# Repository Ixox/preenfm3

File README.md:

# preenFM3

preenFM3 is an open-source FM synthesizer built around an STM32H7 microcontroller.

This repository contains the firmware, the shared hardware library, the bootloader and the hardware design files.

Binaries are available in the [Releases](https://github.com/Ixox/preenfm3/releases) section.  
More user documentation is available in the [Wiki](https://github.com/Ixox/preenfm3/wiki).

## Overview

The firmware runs the FM synth engine, the display UI, MIDI input/output, SD card storage and the bootloader.

The project is split into:

| Folder | Contents |
|--------|----------|
| `firmware/` | Main synth firmware |
| `preen_lib/` | Shared display, input, board and storage library |
| `third_party/` | Vendored HAL, CMSIS, USB, FatFs, SD, display and helper libraries |
| `bootloader/` | Standalone bootloader |
| `hardware/` | PCB and mechanical files |
| `doc/` | Hardware, compilation and improvement notes |

## Hardware at a glance

| Subsystem | Details |
|-----------|---------|
| MCU | STM32H753VITx, Cortex-M7, 480 MHz |
| Audio output | 3 × CS4344 stereo DACs, 6 analog outputs |
| Audio transport | SAI1/SAI2 in I2S mode, DMA, 48 kHz |
| Display | ILI9341, 240 × 320 RGB565, SPI1 + DMA2D |
| Storage | microSD card in SPI mode, SPI2 + FatFs |
| Controls | 6 encoders and 12/18 buttons through a 74HC165 chain |
| MIDI | DIN MIDI on USART1 and USB MIDI over OTG FS |
| Memory | RAM_D1 for display, RAM_D2 for DAC/FX, RAM_D2B for FatFs, RAM_D3 for sequencer |

The CPU runs at its rated 480 MHz; it is not overclocked. The ILI9341 SPI bus runs at approximately 32 MHz, above the panel's nominal rating.

See [doc/hardware.md](doc/hardware.md) for the full hardware documentation.

## Building

The project builds with **CMake** at the repository root. The legacy STM32CubeIDE project files remain in the tree as reference.

The main firmware build configurations are:

| Configuration | Optimization | Debug |
|---------------|--------------|-------|
| `Debug` | `-Og` | `-g3` |
| `Release` (default) | `-Ofast -fno-strict-aliasing -fno-tree-vectorize -funroll-loops` | `-g0` |

Common build settings:

- Toolchain: GNU Arm Embedded (`arm-none-eabi-`), validated with `arm-none-eabi-gcc` 16.2.0
- MCU: `STM32H753VITx`
- Defines: `USE_HAL_DRIVER`, `STM32H753xx`
- Firmware linker script: `firmware/preenfm3_2MB.ld`
- Bootloader linker script: `bootloader/STM32H753VITX_FLASH.ld`

### CMake

Requirements:

- CMake 3.20 or newer
- `arm-none-eabi-gcc` — validated with version 16.2.0
- `arm-none-eabi-newlib` — validated with version 4.6.0.20260123

Configure and build:

```bash
cmake -S . -B build -DCMAKE_TOOLCHAIN_FILE=cmake/arm-none-eabi.cmake
cmake --build build
```

This builds both `preenfm3_firmware` and `preenfm3_bootloader`. The default `Release` build produces `build/firmware/p3_<version>.bin` and `build/bootloader/p3_boot_<version>.bin`, along with the `.elf`, `.bin` and `.hex` artifacts. The firmware version comes from `firmware/include/version.h` (currently `v1.04`, so `p3_1_04.bin`); the bootloader version comes from `bootloader/include/version.h`.

### Flashing

There are two separate operations: flashing the **bootloader** (only needed once, or to upgrade it) and flashing the **firmware**.

To boot into the bootloader, hold down the **MENU** button while turning the preenFM3 on.

#### Bootloader (first-time / never-flashed board)

The bootloader lives at `0x08000000` and must be installed before the firmware can be updated normally. On a board that has never been flashed, put the MCU in DFU mode with the switch on the back of the PCB, then flash the bootloader:

```bash
dfu-util -a 0 -d 0x0483:0xdf11 \
  -D build/bootloader/p3_boot_1_10.bin -s 0x08000000
```

Alternatively, use ST-LINK through the 4-pin header on the back of the PCB; see [doc/stlink.md](doc/stlink.md).

Once the bootloader has been flashed, you can enter DFU mode from the bootloader itself, or keep using the ST-LINK 4-pin header.

#### Firmware (normal update)

The preferred method is the SD card:

1. Put `build/firmware/p3_<version>.bin` (for example `p3_1_04.bin`) on the SD card.
2. Boot the bootloader and flash the file from the SD card.

If the SD card is not accessible, the bootloader can expose it to a computer as a USB mass-storage device, so the firmware `.bin` can be copied without removing the card.

Firmware updates can also be done over DFU from the bootloader:

```bash
dfu-util -a 0 -d 0x0483:0xdf11 \
  -D build/firmware/p3_1_04.bin -s 0x08020000
```

Finally, the firmware can be written directly with ST-LINK through the 4-pin header on the back of the PCB:

```bash
st-flash --reset write build/firmware/p3_1_04.bin 0x08020000
```

See [doc/stlink.md](doc/stlink.md) for ST-LINK setup and troubleshooting.

### Project status

The source tree has been reorganized into `firmware/`, `preen_lib/`, `third_party/` and `bootloader/`. The CMake build now produces the full firmware and bootloader; the CubeIDE `.cproject` files are no longer the primary build.

See [doc/compilation.md](doc/compilation.md) for detailed build information and the CMake migration plan.

## Documentation

- [Hardware documentation](doc/hardware.md)
- [Compilation and CMake migration](doc/compilation.md)
- [Known improvements](doc/improvements.md)
- [Project Wiki](https://github.com/Ixox/preenfm3/wiki)

## License

The firmware is distributed under the GNU General Public License v3. See [LICENSE](LICENSE) for the full text and [third_party/NOTICE](third_party/NOTICE) for third-party licensing. See the source file headers for details.

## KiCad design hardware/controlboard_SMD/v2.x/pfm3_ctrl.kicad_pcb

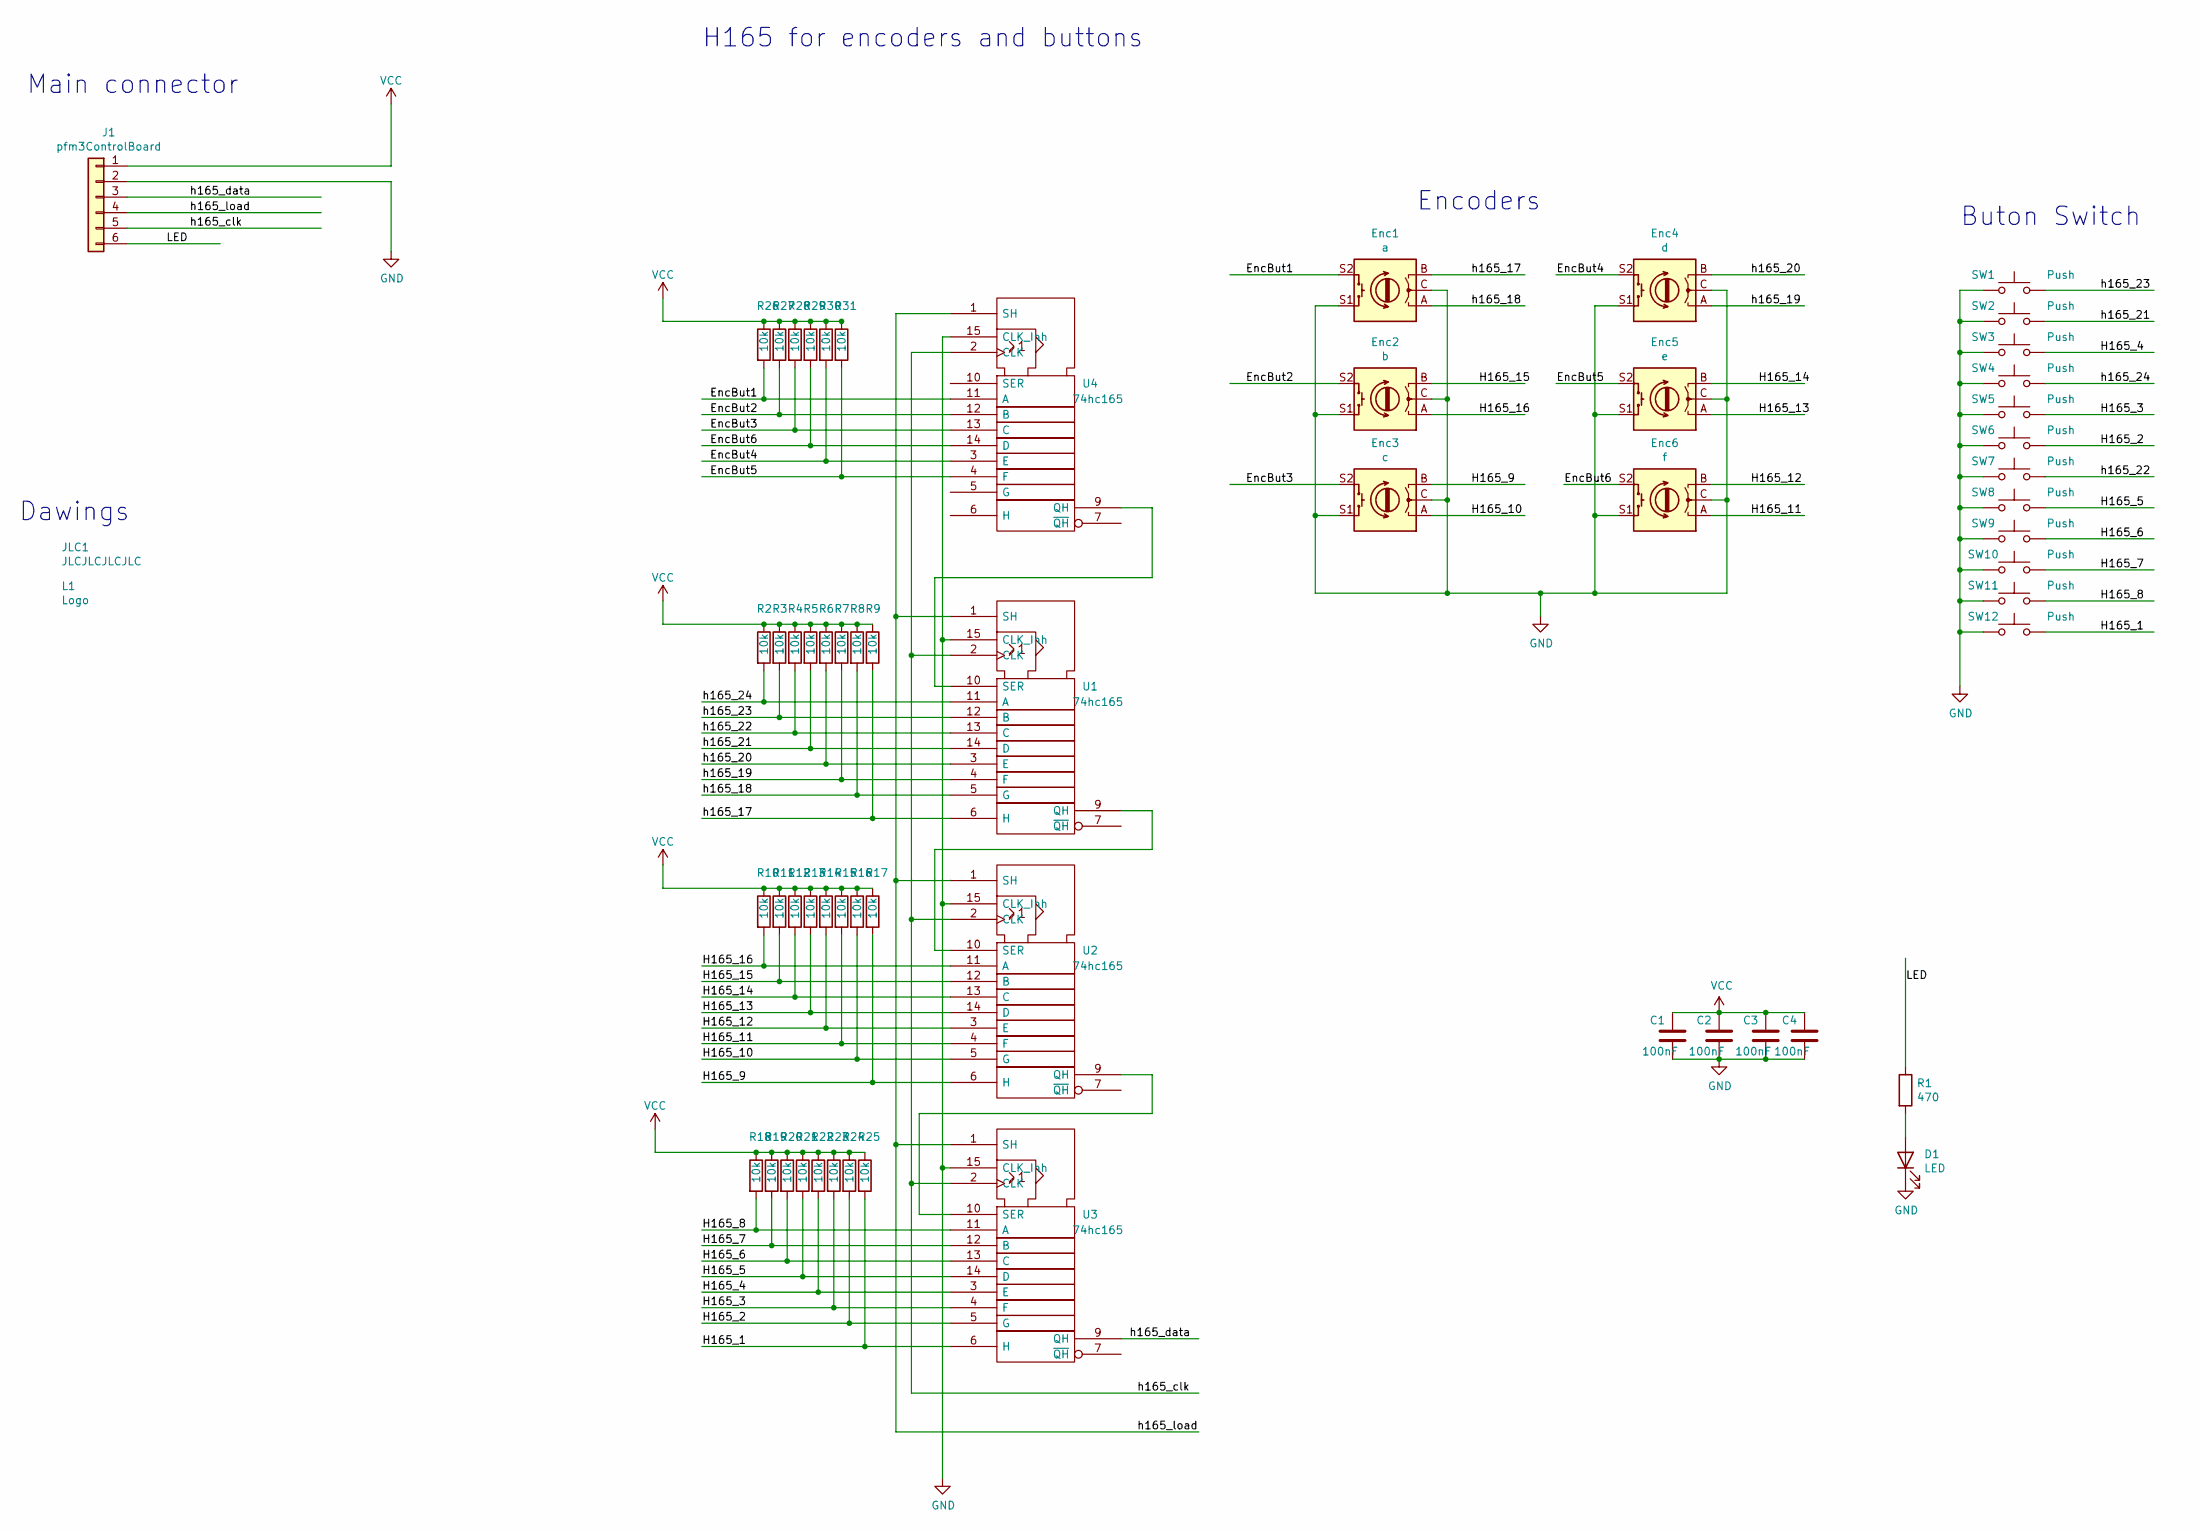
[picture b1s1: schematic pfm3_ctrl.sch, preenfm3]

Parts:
C1, C2, C3, C4: 100nF; C_0402_1005Metric
D1: LED; LED_0603_1608Metric
Enc1: a; FMEncoder2_pfm3
Enc2: b; FMEncoder2_pfm3
Enc3: c; FMEncoder2_pfm3
Enc4: d; FMEncoder2_pfm3
Enc5: e; FMEncoder2_pfm3
Enc6: f; FMEncoder2_pfm3
J1: pfm3ControlBoard; ControlBoard_2
JLC1: JLCJLCJLCJLC; JLCJLC
L1: Logo; pfm2_logo
R1: 470; R_0603_1608Metric
R2, R3, R4, R5, R6, R7, R8, R9, R10, R11, R12, R13, R14, R15, R16, R17, R18, R19, R20, R21, R22, R23, R24, R25, R26, R27, R28, R29, R30, R31: 10k; R_0402_1005Metric
SW1, SW2, SW3, SW4, SW5, SW6, SW7, SW8, SW9, SW10, SW11, SW12: Push; FMButton2
U1, U2, U3, U4: 74hc165; SOIC-16_3.9x9.9mm_P1.27mm

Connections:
/EncBut1: Enc1.S2, R26.2, U4.11 (A)
/EncBut2: Enc2.S2, R27.2, U4.12 (B)
/EncBut3: Enc3.S2, R28.2, U4.13 (C)
/EncBut4: Enc4.S2, R30.2, U4.3 (E)
/EncBut5: Enc5.S2, R31.2, U4.4 (F)
/EncBut6: Enc6.S2, R29.2, U4.14 (D)
/H165_1: R25.2, SW12.2, U3.6 (H)
/H165_2: R24.2, SW6.2, U3.5 (G)
/H165_3: R23.2, SW5.2, U3.4 (F)
/H165_4: R22.2, SW3.2, U3.3 (E)
/H165_5: R21.2, SW8.2, U3.14 (D)
/H165_6: R20.2, SW9.2, U3.13 (C)
/H165_7: R19.2, SW10.2, U3.12 (B)
/H165_8: R18.2, SW11.2, U3.11 (A)
/H165_9: Enc3.B, R17.2, U2.6 (H)
/H165_10: Enc3.A, R16.2, U2.5 (G)
/H165_11: Enc6.A, R15.2, U2.4 (F)
/H165_12: Enc6.B, R14.2, U2.3 (E)
/H165_13: Enc5.A, R13.2, U2.14 (D)
/H165_14: Enc5.B, R12.2, U2.13 (C)
/H165_15: Enc2.B, R11.2, U2.12 (B)
/H165_16: Enc2.A, R10.2, U2.11 (A)
/LED: J1.6, R1.1
/h165_17: Enc1.B, R9.2, U1.6 (H)
/h165_18: Enc1.A, R8.2, U1.5 (G)
/h165_19: Enc4.A, R7.2, U1.4 (F)
/h165_20: Enc4.B, R6.2, U1.3 (E)
/h165_21: R5.2, SW2.2, U1.14 (D)
/h165_22: R4.2, SW7.2, U1.13 (C)
/h165_23: R3.2, SW1.2, U1.12 (B)
/h165_24: R2.2, SW4.2, U1.11 (A)
/h165_clk: J1.5, U1.2 (CLK), U2.2 (CLK), U3.2 (CLK), U4.2 (CLK)
/h165_data: J1.3, U3.9 (QH)
/h165_load: J1.4, U1.1 (SH), U2.1 (SH), U3.1 (SH), U4.1 (SH)
GND: C1.2, C2.2, C3.2, C4.2, D1.1 (K), Enc1.C, Enc1.S1, Enc2.C, Enc2.S1, Enc3.C, Enc3.S1, Enc4.C, Enc4.S1, Enc5.C, Enc5.S1, Enc6.C, Enc6.S1, J1.2, SW1.1, SW2.1, SW3.1, SW4.1, SW5.1, SW6.1, SW7.1, SW8.1, SW9.1, SW10.1, SW11.1, SW12.1, U1.8 (GND), U1.15 (CLK_Inh), U2.8 (GND), U2.15 (CLK_Inh), U3.8 (GND), U3.15 (CLK_Inh), U4.8 (GND), U4.15 (CLK_Inh)
unnamed: D1.2 (A), R1.2
unnamed: U1.9 (QH), U2.10 (SER)
unnamed: U1.10 (SER), U4.9 (QH)
unnamed: U2.9 (QH), U3.10 (SER)
VCC: C1.1, C2.1, C3.1, C4.1, J1.1, R2.1, R3.1, R4.1, R5.1, R6.1, R7.1, R8.1, R9.1, R10.1, R11.1, R12.1, R13.1, R14.1, R15.1, R16.1, R17.1, R18.1, R19.1, R20.1, R21.1, R22.1, R23.1, R24.1, R25.1, R26.1, R27.1, R28.1, R29.1, R30.1, R31.1, U1.16 (VCC), U2.16 (VCC), U3.16 (VCC), U4.16 (VCC)

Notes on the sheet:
Buton Switch
Encoders
H165 for encoders and buttons
Main connector
Dawings

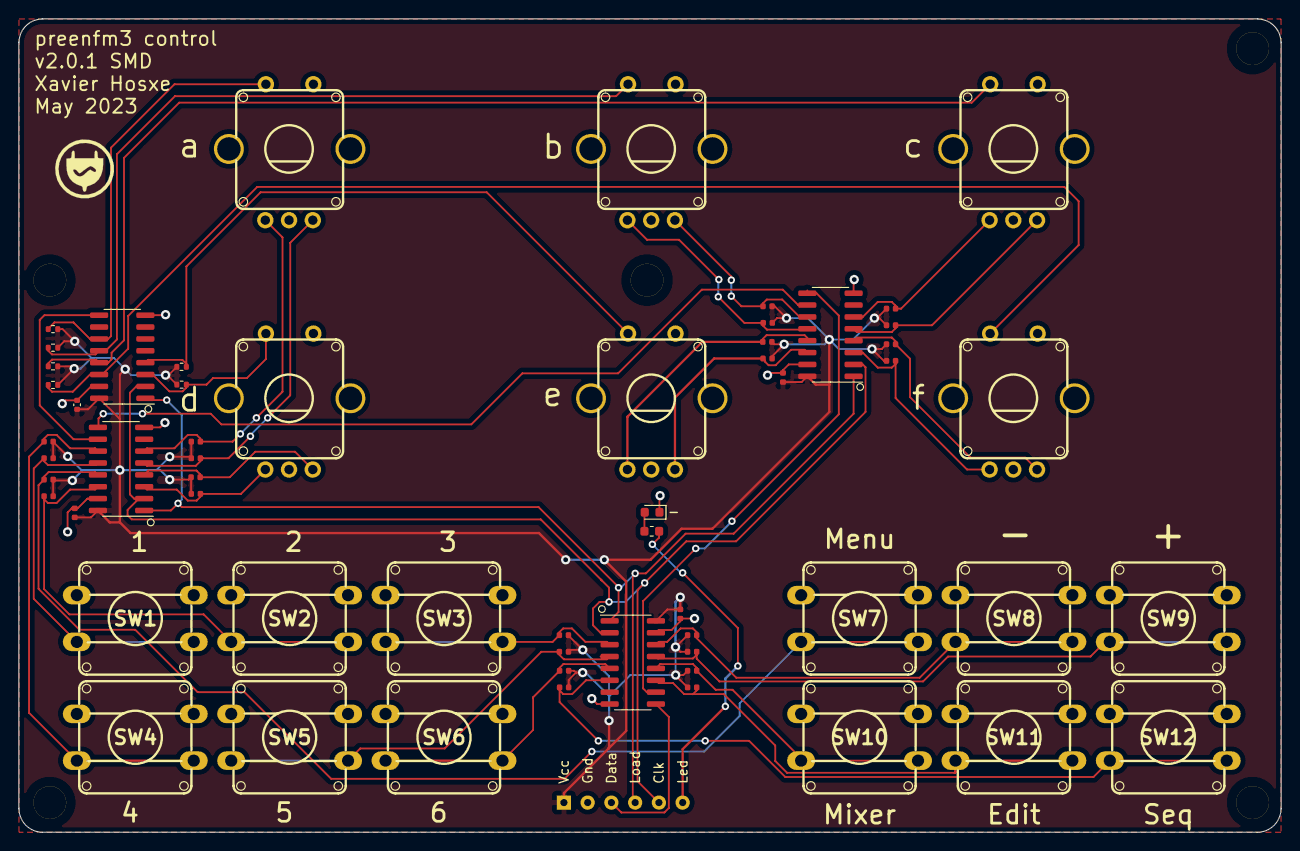
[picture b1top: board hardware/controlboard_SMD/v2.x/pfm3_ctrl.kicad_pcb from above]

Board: 2 copper layers, 135.0 x 87.0 mm, 61 parts (1 on the bottom side), 40 nets.

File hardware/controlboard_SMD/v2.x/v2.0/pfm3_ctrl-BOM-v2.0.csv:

"Id","Designator","Footprint","Quantity","Comment","LCSC part number"
"8","U4,U3,U2,U1","SOIC-16_3.9x9.9mm_P1.27mm","4","74hc165","C5613"
"9","R31,R30,R29,R28,R27,R26,R25,R24,R23,R22,R21,R20,R19,R18,R17,R16,R15,R14,R13,R12,R11,R10,R9,R8,R7,R6,R5,R4,R3,R2","R_0402_1005Metric","30","10k","C25744"
"10","C4,C3,C2,C1","C_0402_1005Metric","4","100nF","C1525"
"14","R1","R_0603_1608Metric","1","470","C23179"
"15","D1","LED_0603_1608Metric","1","LED","C72041"

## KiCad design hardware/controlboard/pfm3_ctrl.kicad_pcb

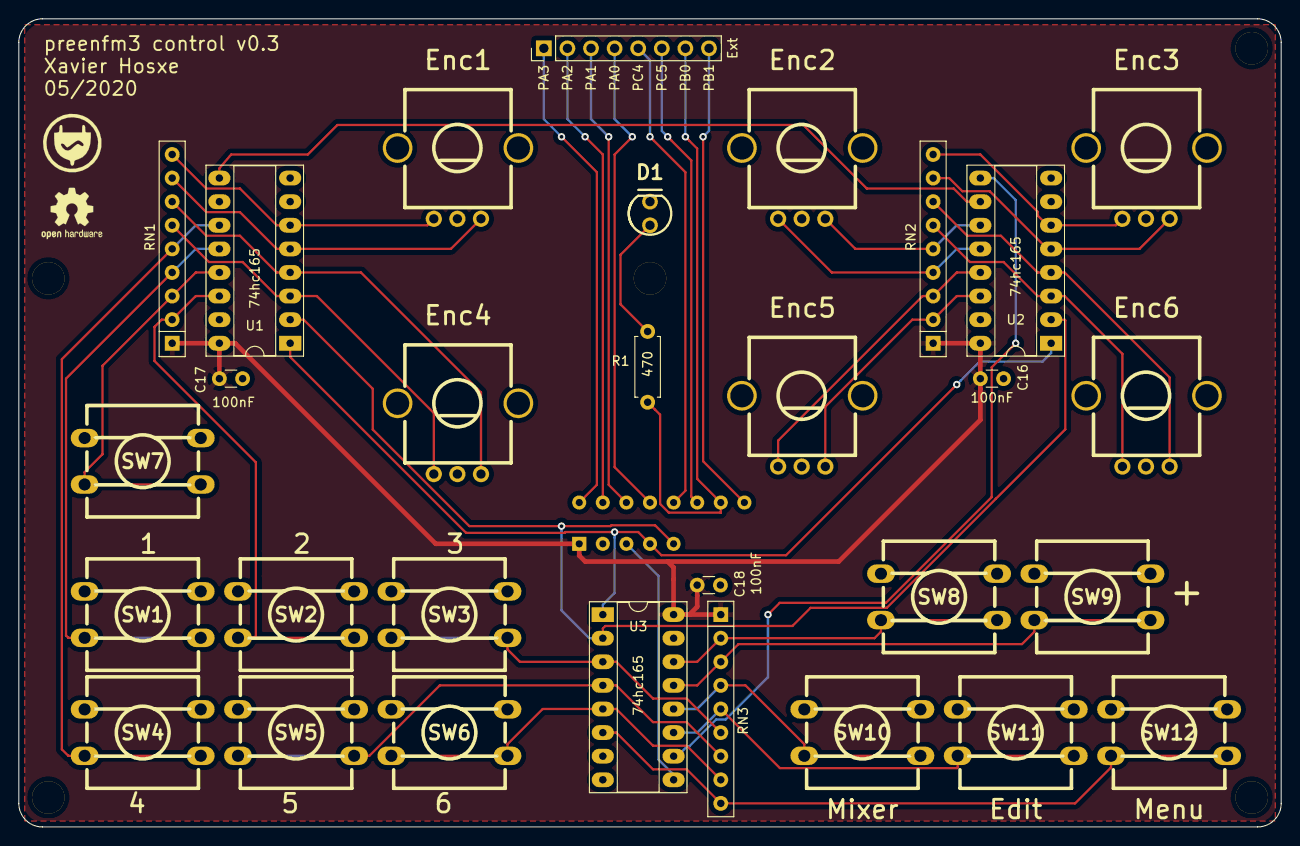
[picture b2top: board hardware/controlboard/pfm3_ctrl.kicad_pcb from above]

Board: 2 copper layers, 135.9 x 87.0 mm, 31 parts (0 on the bottom side), 40 nets.

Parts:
C16, C17, C18: 100nF; C_Disc_D3.0mm_W1.6mm_P2.50mm
CB1: pfm3ControlBoard; ControlBoard
D1: LED; FMLed_pfm3
Enc1, Enc2, Enc3, Enc4, Enc5, Enc6: Encoder; FMEncoder2_pfm3
J1: Ext; PinHeader_1x08_P2.54mm_Vertical
R1: 470; R_Axial_DIN0207_L6.3mm_D2.5mm_P7.62mm_Horizontal
RN1, RN2, RN3: Net8; R_Array_SIP9
SW1, SW2, SW3, SW4, SW5, SW6, SW7, SW8, SW9, SW10, SW11, SW12: Push; FMButton2
U1, U2, U3: 74hc165; 74HC165

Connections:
/H165_1: RN3.9, SW12.2, U3.6
/H165_2: RN3.8, SW6.2, U3.5
/H165_3: RN3.7, SW5.2, U3.4
/H165_4: RN3.6, SW3.2, U3.3
/H165_5: RN3.2, SW8.2, U3.14
/H165_6: RN3.3, SW9.2, U3.13
/H165_7: RN3.4, SW10.2, U3.12
/H165_8: RN3.5, SW11.2, U3.11
/H165_9: Enc3.B, RN2.9, U2.6
/H165_10: Enc3.A, RN2.8, U2.5
/H165_11: Enc6.A, RN2.7, U2.4
/H165_12: Enc6.B, RN2.6, U2.3
/H165_13: Enc5.A, RN2.2, U2.14
/H165_14: Enc5.B, RN2.3, U2.13
/H165_15: Enc2.B, RN2.4, U2.12
/H165_16: Enc2.A, RN2.5, U2.11
/PB0: CB1.12, J1.7, R1.1
/h165_17: Enc1.B, RN1.9, U1.6
/h165_18: Enc1.A, RN1.8, U1.5
/h165_19: Enc4.A, RN1.7, U1.4
/h165_20: Enc4.B, RN1.6, U1.3
/h165_21: RN1.2, SW2.2, U1.14
/h165_22: RN1.3, SW7.2, U1.13
/h165_23: RN1.4, SW1.2, U1.12
/h165_24: RN1.5, SW4.2, U1.11
/h165_clk: CB1.5, U1.2, U2.2, U3.2
/h165_data: CB1.3, U3.9
/h165_load: CB1.4, U1.1, U2.1, U3.1
GND: C16.2, C17.2, C18.2, CB1.2, D1.1, Enc1.C, Enc2.C, Enc3.C, Enc4.C, Enc5.C, Enc6.C, SW1.1, SW2.1, SW3.1, SW4.1, SW5.1, SW6.1, SW7.1, SW8.1, SW9.1, SW10.1, SW11.1, SW12.1, U1.8, U1.15, U2.8, U2.15, U3.8, U3.15
unnamed: CB1.6, J1.1
unnamed: CB1.7, J1.2
unnamed: CB1.8, J1.3
unnamed: CB1.9, J1.4
unnamed: CB1.10, J1.5
unnamed: CB1.11, J1.6
unnamed: CB1.13, J1.8
unnamed: D1.2, R1.2
unnamed: U1.9, U2.10
unnamed: U2.9, U3.10
VCC: C16.1, C17.1, C18.1, CB1.1, RN1.1, RN2.1, RN3.1, U1.16, U2.16, U3.16

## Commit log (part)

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2020-09-10 First public commit
2020-09-12 Update headers + fix save preset and create preset bank
2020-09-22 Control board PCB added
2020-09-27 Last choice remembered in Menu + program change store bank and preset
2020-09-27 Menu : don't crash when empty button are pressed
2020-09-28 Silently load preset / DMA access to SD card
2020-09-28 Fix voice allocation problem while browsing preset
2020-09-30 3D case added
2020-09-30 Finaly
2020-10-05 Fix feedback + fix problem with output number
2020-10-06 MENU + PREV_INSTR = Reinit TFT
2020-10-07 Bootloader fixed : SD access don't use DMA
2020-10-07 Allow -O3 on preenfm3_lib
2020-10-13 3DCaseB added
2020-10-21 Faster encoder polling
2020-10-21 Add colors after reinit TFT
2020-10-21 Sequencer V2 + many small fixes
2020-10-24 Sequencer has its own default file
2020-10-25 Fix seq cursor refresh bug
2020-10-25 Better Seq presentation
2020-10-25 No more DEBUG preprocessing in Release
2020-10-25 Create object use _ in bin names
2020-10-25 Bootloader 1.02 : use button 1,2,3
2020-10-27 Limit SD SPI to 12.5Mhz (will use actually 7.5Mhz)
2020-10-27 Tiny type fix
2020-10-31 doc/README added
2020-10-31 Fix quick start doc
2020-11-03 Slower and much more stable UI with some TFTs
2020-11-04 Bootlader 1.03 TFT fixed
2020-11-08 Control board v1.1
2020-11-08 Small display optimization and stability
2020-11-08 Modification to use last lib
2020-11-08 v0.94 first commit
2020-11-08 Multiple edition show up in green
2020-11-08 Fix buton state bug (Crash)
2020-11-08 Remove Debug info from Release
2020-11-10 Put back to fast 40mbit/s SPI TFT communication
2020-11-10 Limit the operator navigation to the available ones
2020-11-10 Fix the voice problem when browsing the preset or randomize
2020-11-10 PCB 1.3 : encoder 2 moved 1mm
2020-11-10 version.h v095
2020-11-13 Bootloader 1.05 : SD card access from computer
2020-11-14 SD access back to 15Mhz which is fine with ALL SD card
2020-11-14 Fix active timbre detection and voice realocation after preset change
2020-11-15 New static volume behaviour
2020-11-19 PCB controlboard 1.2 proto
2020-11-20 Compressor per instrument
2020-11-20 Add colors
2020-11-20 Better scale
2020-11-20 Reinit compressors after mixer load
2020-11-20 nicer level metter color
2020-11-21 Compressor default value + optimm metter refresh + clean
2020-11-21 Fix sequencer step problem when recording while swaping between normal and step mode.
2020-11-21 Level metters added in editor and in sequencer
2020-11-21 Bootloader 1.06 : fix SD card access under windows when capacity > 4GB
2020-11-21 1024 seems to have widerr SD card compatibility
2020-11-21 Start refactoring member variables '_' + sequencer bug fix + meter level global option
2020-11-22 Improve UI and colors
2020-11-22 Scala scale Instr 0 Fix + Sala scale better display
2020-11-22 Scala scale : not mapped notes are silent
2020-11-22 Oscillo can scale up to x4
2020-11-22 Better new preset
2020-11-22 Editor instrument name in WHITE
2020-11-22 Fix new preset loading + clean
2020-11-25 v0.97b : fix freeze when reubuilding timbre/voice association
2020-11-25 First unison commit
2020-11-26 Mixer>Voices : RED if problem with instrument poly/mono/unison mode
2020-11-26 Fix MULTI-edit in operator envs
2020-11-28 TFT stability (slower, higher priority, smaller chunks for DMA push)
2020-11-28 Clean up and decrease noise (slower GPIO, OLD PCB pinout, TFT backlight removed, MDMA)
2020-11-29 New creat_object scripts
2020-11-29 Stop argegiator when sequencer is stopped
2020-11-30 v0.98b : fix NRPN & preset save
2020-11-30 Scripts : Accept one letter in version regexp
2020-12-04 Add 6 buttons for encoder switches
2020-12-04 Add async action for loading presets and flushing NRPNs
2020-12-04 v099 : TFT Auto Reinit
2020-12-05 Fixed UNISON, which was totally broken in v0.98
2020-12-05 Add option for futur Encoder Switch and cleaning
2020-12-06 glide now contains off (legacy Speed 0) : much more clear
2020-12-06 Voices renamed Mode
2020-12-06 Small changes after PR review
2020-12-08 Scala loading based on scale name fixed
2020-12-13 New operator navigation + CC74 + RandK + IM Feedback in matrix
2020-12-13 v0.100 + Editor>Oper>Env rename
2020-12-13 Don't crash when select clickable encoder with NO clicabke encoder
2020-12-13 User CC + Poly AfterTouch (channel pressure) + sequencer drives MidiClocked LFO
2020-12-14 Sequencer sends midi tic (24/beat) should work with Arpegiator (not tested)
2020-12-16 Seqencer : fixe some cases where the Arpegiator continue after we stop playing
2020-12-16 UI: Add Sync (Int/Ext) to modulator LFO and Step seq
2020-12-18 Usb midi was filtering out PolyAfter touch data
2020-12-18 Renamed ChannelPressure to PolyAfterTouch
2020-12-19 TFT pins speed : HIGH is up to 100Mhz so it's OK and less noisy
2020-12-19 Better TFT white screen detection & OFF option really OFF
2020-12-19 Decrease a little (40 to 32Mhz) the TFT SPI freq allow more consistant buffer reading
2020-12-19 Add 2 new TFT read status method
2020-12-19 E d i t o r : CYAN
2020-12-19 MEDIUM GPIO speed : timing adjusment - See table 63 Of STM332H743 datasheet
2020-12-20 Mixer Voices/compressor/Out reordered
2020-12-20 Fix 2 mixer state problems in new created Mixer Bank
2020-12-24 Arp in preset is now On by default + add a button to move forward when enering new name
2020-12-25 Voice index bug fixed + Instr +&- now realyy stop all sounds
2020-12-25 Fix wrong test that make note=255 and cannot be stoped
2020-12-31 UsbMidi flush fixed + different buffer for In and Out
2021-01-02 Better Encoder scan timing
2021-01-02 Small fix in Polyphonic voice choser
2021-01-02 Fixed typo in constant name
2021-01-02 Play notes even when noteOff is received during QuickRelease of previous note + fix variable initialization problem when playing note the very first time
2021-01-03 Last cleanup and misc IDE files before v0.102
2021-01-07 Communication OK with the editor (USB & DIN)
2021-01-10 Rename CHANNEL_PRESSURE to POLYPHONIC_AFTERTOUCH
2021-01-10 Fix version string length
2021-01-10 V0.103 : Ready for the editor
    * Ready for the Editor (USB & UI fixed)
    * Rename CHANNEL_PRESSURE to POLYPHONIC_AFTERTOUCH
2021-01-17 Case B information updated
2021-01-17 Feedback target divided by 16
2021-01-17 Midi polyphonic after touch takes Midi note shift into account
2021-01-26 Sequencer load fix + first notes fixed
2021-01-26 Mixer back to old fashion + Mixer UI improved
2021-04-03 Detune phase + unison midi + TFT backlight
2021-04-05 Instrument1 MPE
2021-04-06 v107 beta2 : renaming + pitch bend MPE fixed
2021-04-16 v0.107b3 : MPE ready ?
2021-04-17 New enclosure added (3D printed + PCB)
2021-04-18 3DCasePCB add spacers/screws/nuts list
2021-04-18 v0.107 official
2021-09-03 Original version from pvig
2021-09-03 Integration first modifications
2021-09-04 All reverb params available (if ReverbParams set to Show)
2021-09-04 Call fxBus init after constructors
2021-09-05 paramChanged() smoothing removed
2021-09-05 reverb param order
2021-10-16 predelay & lfo bug fix
2021-10-17 bug fix & reverb param order
2021-10-17 Firmware 1.08b : reverb fix
2021-10-21 filter param2 in matrix
2021-10-22 some fix
2021-10-23 bass & pan fix
2021-10-23 param2 for crusher
2021-10-23 New MB LQFP100 + seq controled by midi
2021-10-24 filter amp in modmatrix
2021-10-24 Filter param 2 in the matrix (#22)
    * filter param2 in matrix
    * wip
    * some fix
    * bass & pan fix
    * param2 for crusher
    * cleaning
2021-10-24 New MB LQFP100 + seq controled by midi (#23)
2021-10-24 Smoother dry/wet reverb
2021-10-25 cosine x-mix
2021-10-30 bootloader v1.09 can jump to other adress
2021-10-30 Firmware v0.109 optimization flag -Ofast (used to be -O3)
2022-03-30 loop is back
2022-04-18 Midi controller first version
2022-04-18 Dedicated MidiController folder
2022-04-18 Copy and Past in Editor
2022-04-18 Encoder clean state function
2022-04-18 Menu+Seq switches between pfm3 and controller mode
2022-04-18 Letter shortcut with button
2022-04-18 Midi controller new/better keys
2022-07-09 Fix Possible noise when modifying MIX param
2022-10-19 first test
2022-10-19 menu
2022-10-20 usable curves
2022-10-23 curve on each env
2022-10-23 envUsr4
2022-10-25 env curve user file load
2022-10-27 usr env files load fix
2022-11-01 usr files load fix
2022-11-05 same on fxbus side
2022-11-06 missing code
2022-11-06 reverb slowParamChange
2022-11-08 save envcurve to flash
2022-11-10 spaces
2022-11-12 Fix Crash in Oscilloscope with very low frequency + negative fine tune (THANKS PATRICE git add firmware/Src/synth/Osc.cpp! :)
2022-11-12 LP on mix change when in MPE mode
2022-11-12 Add space after C keywords
2022-11-14 drunky lfo
2022-11-15 some more shapes
2022-11-15 keep sign
2022-11-16 gaussian with LP
2022-11-16 names
2022-11-17 key start
2022-11-27 ControlBoard : Move files into v1 folder
2022-11-27 Control board v2
2022-11-28 v2.0 JLCPCB ordered for test
2022-11-30 v1.2 encpder and switch positions with v2.0 connector
2022-12-24 Push misc xml and shell files
2022-12-24 Add more LFO shapes
2022-12-24 User Env Curve
2022-12-26 version.h 0.113
2022-12-31 Refactor/simplify envelope memory structures
2023-01-01 Display real envelopes in OscilloBG
2023-01-01 Fix bug after Env refactor (Midi and Menu+enc) / Version set to 0.990
2023-01-02 Fix NRPN from editor + bug fix + drawing optimization
2023-01-03 Improve/Fix env refresh
2023-01-04 Fix env release set to 0 when saved
2023-01-04 Fix CC problem after env refactoring
2023-02-04 Note and Velo modification in step sequencer
2023-02-05 Note + Encoder can create note when cursor over silence
2023-04-03 More FX by Toltekradiation
2023-04-04 Fix before merge
2023-04-10 bode & doubler
2023-04-12 3Voices hp remove
2023-04-15 pitch shift optimisation
2023-04-15 bug fix : avoid filters blow up
2023-04-18 fx sort
2023-04-18 Doubler rework, wide eq
2023-04-23 cleanup & tweak
2023-04-28 Filters: optimisation and bug fix
    Optimisation : less cpu for Wide, Dblr, 3Voi
    Bug fix : avoid explode of filters in some extreme case
    Enhancement : EQ on some filters, to get bass back
    Change filters order
2023-05-12 Fix Level>1.0 problem
2023-05-13 New FX2 menu and modulation for the new paraphonic FX
2023-05-15 Small control board PCB modification: wider clearance around placement holes
2023-05-21 ping & diff extra lp, doubler level fix
2023-05-21 ping & diff aliasing
2023-05-21 diff click, ping cutoff, cleaning
2023-05-22 Fix Copy and Paste
2023-05-22 levels
2023-05-24 Fix crash when copying empty params
2023-05-24 Revert "var cleaning"
    This reverts commit b8b72e475ff28883c0ad3dcc3f0dbfc4dd6e1664.
2023-05-25 more cleaning & delay fdbck lp bump
2023-05-25 diff bug fix
2023-05-27 Diff finetuning
2023-05-27 Versin 1.00 git add firmware/Inc/version.h
2023-06-10 more delay feedback
2023-06-10 delay f square control
2023-06-13 grain : quartic spread
2023-06-14 cleanup, bug fix & grain2 tuning
2023-06-16 grain onset
2023-06-18 v1.01 fix preset name problem with the VST editor
2023-06-20 grain tweak
2023-06-23 grain hold mode trig
2023-06-24 ram optim
2023-06-25 lock fix
2023-07-05 delay hp, grain2 lp
2023-07-08 code cleaning & ram optimisation
2023-07-09 flanger rework
2023-07-09 ram optimisation
2023-07-09 ram optim + flanger range fix
2023-07-09 flanger range fix 2
2023-07-13 flange level, chorus bass
2023-07-15 voicesToTimbre micro optimisation
2023-07-30 doubler & bode faster control
2023-08-08 env curve issue after mixer loading
2023-08-09 refreshOscilloBG after mixer load
2023-08-21 FILTER_CRUSHER init bug fix
2023-08-26 doubler : resonance tame
2023-10-08 flanger / dim / chorus rework 1
2023-10-09 dim m/s, chorus bass
2023-10-22 Mixer volume : ENCODER + MENU => modify volumes of all instruments on same DAC
2023-10-22 Fix vtable compilation problem with STM32CubeIDE 1.10
2023-10-22 anti click transition on fx change
2023-10-22 Patrice Vigouroux effects improvement (Granul2) (#43)
    * ok
    * more delay feedback
    * delay f square control
    * hp optimization...
    * grain : quartic spread
    * cleanup, bug fix & grain2 tuning
2023-10-22 v1.02
2024-03-17 Toltekradiation Voisim algos (29->32)
2024-03-17 Adjust phase when resyncing
2024-03-17 Small cleaning
